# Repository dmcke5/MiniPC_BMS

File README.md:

# MiniPC BMS
A tiny UPS for powering Mini PC's from battery!

## Features:
- USB-C PD charging
- Secondary charger input
- USB-HID UPS communication to provide the operating system with battery information
- Inbuilt fuel gauge IC for accurate battery capacity monitoring
- Extremely low powered-down power consumption (5.1uA)
- Inbuilt 19v boost for stable output at up to 3A.
- Solid state switch for triggering PC power button

## Software:
The software for this project is based on this HID power device library:
https://github.com/abratchik/HIDPowerDevice

The software is complete and functional, although it could use some polish and some comments.
I would recommend changing the "debug" variable in MiniPC_UPS.ino to true before you flash the code for the first time.
This will enable debug output and stop the BMS from trying to shut your computer down due to a "Low battery".
Once you've confirmed all of the values are being read correctly, you should be safe to go back in and set that variable to false
and the BMS will begin functioning.

## Known issues

USB-C PD charging is slow. I found a small issue in the PCB design (which I have now fixed) before uploading that may or may not have solved this problem. I suspect that the issues I've had with this are just down to soldering or faulty hardware because the second charger input works as intended and it is basically identical to the first one after all of the USB PD components. I have checked and the correct values are being requested from the USB charger so the issue has somewhere down the line from the USB PD hardware. This was working for me at one stage, which is why I suspect its an assembly issue.

USB HID is sometimes not detected by windows. This one has been difficult to track down, but I'm certain its a software issue that's causing the problem. A simple restart of the system always seems to rectify the problem so I've left it alone for now.

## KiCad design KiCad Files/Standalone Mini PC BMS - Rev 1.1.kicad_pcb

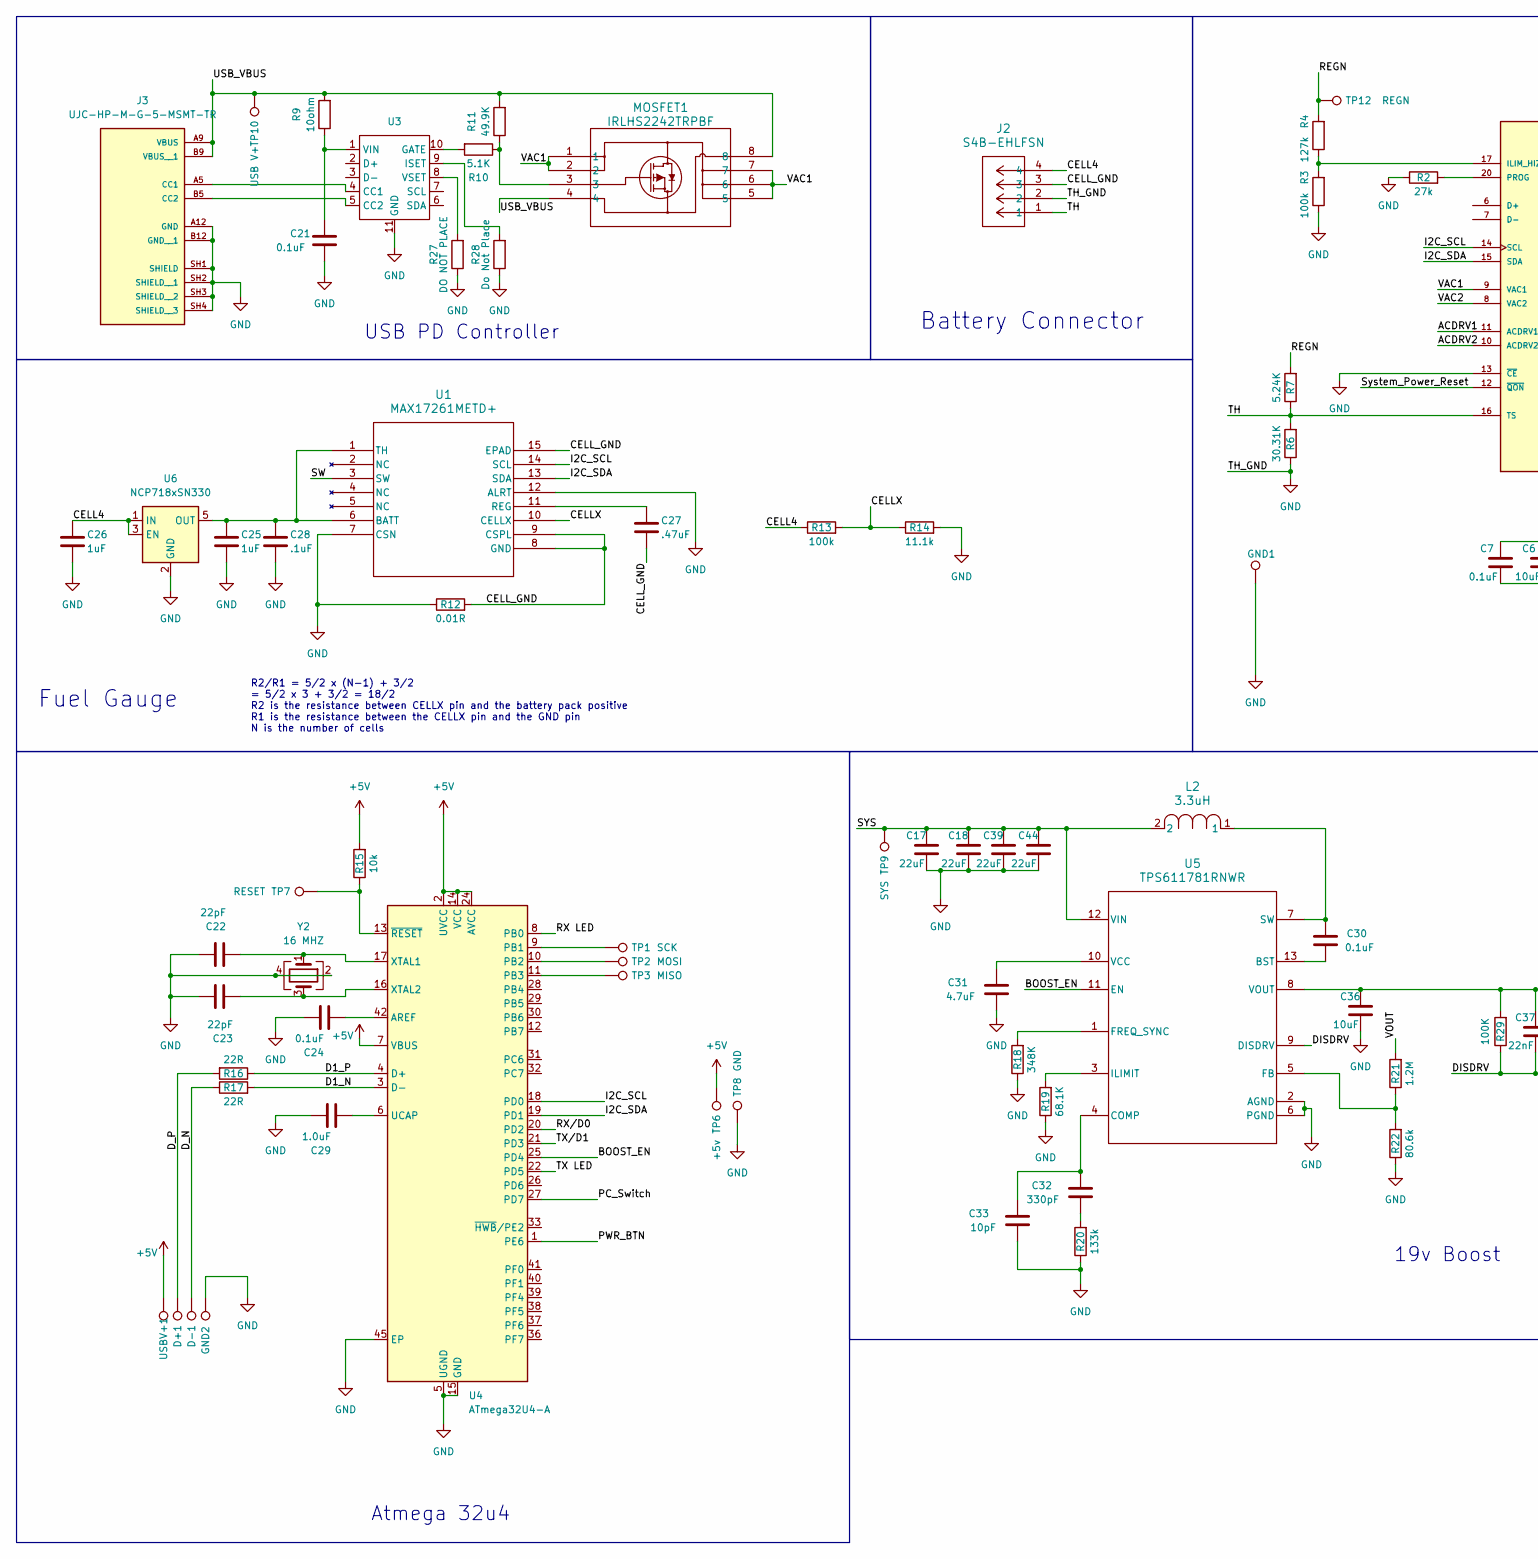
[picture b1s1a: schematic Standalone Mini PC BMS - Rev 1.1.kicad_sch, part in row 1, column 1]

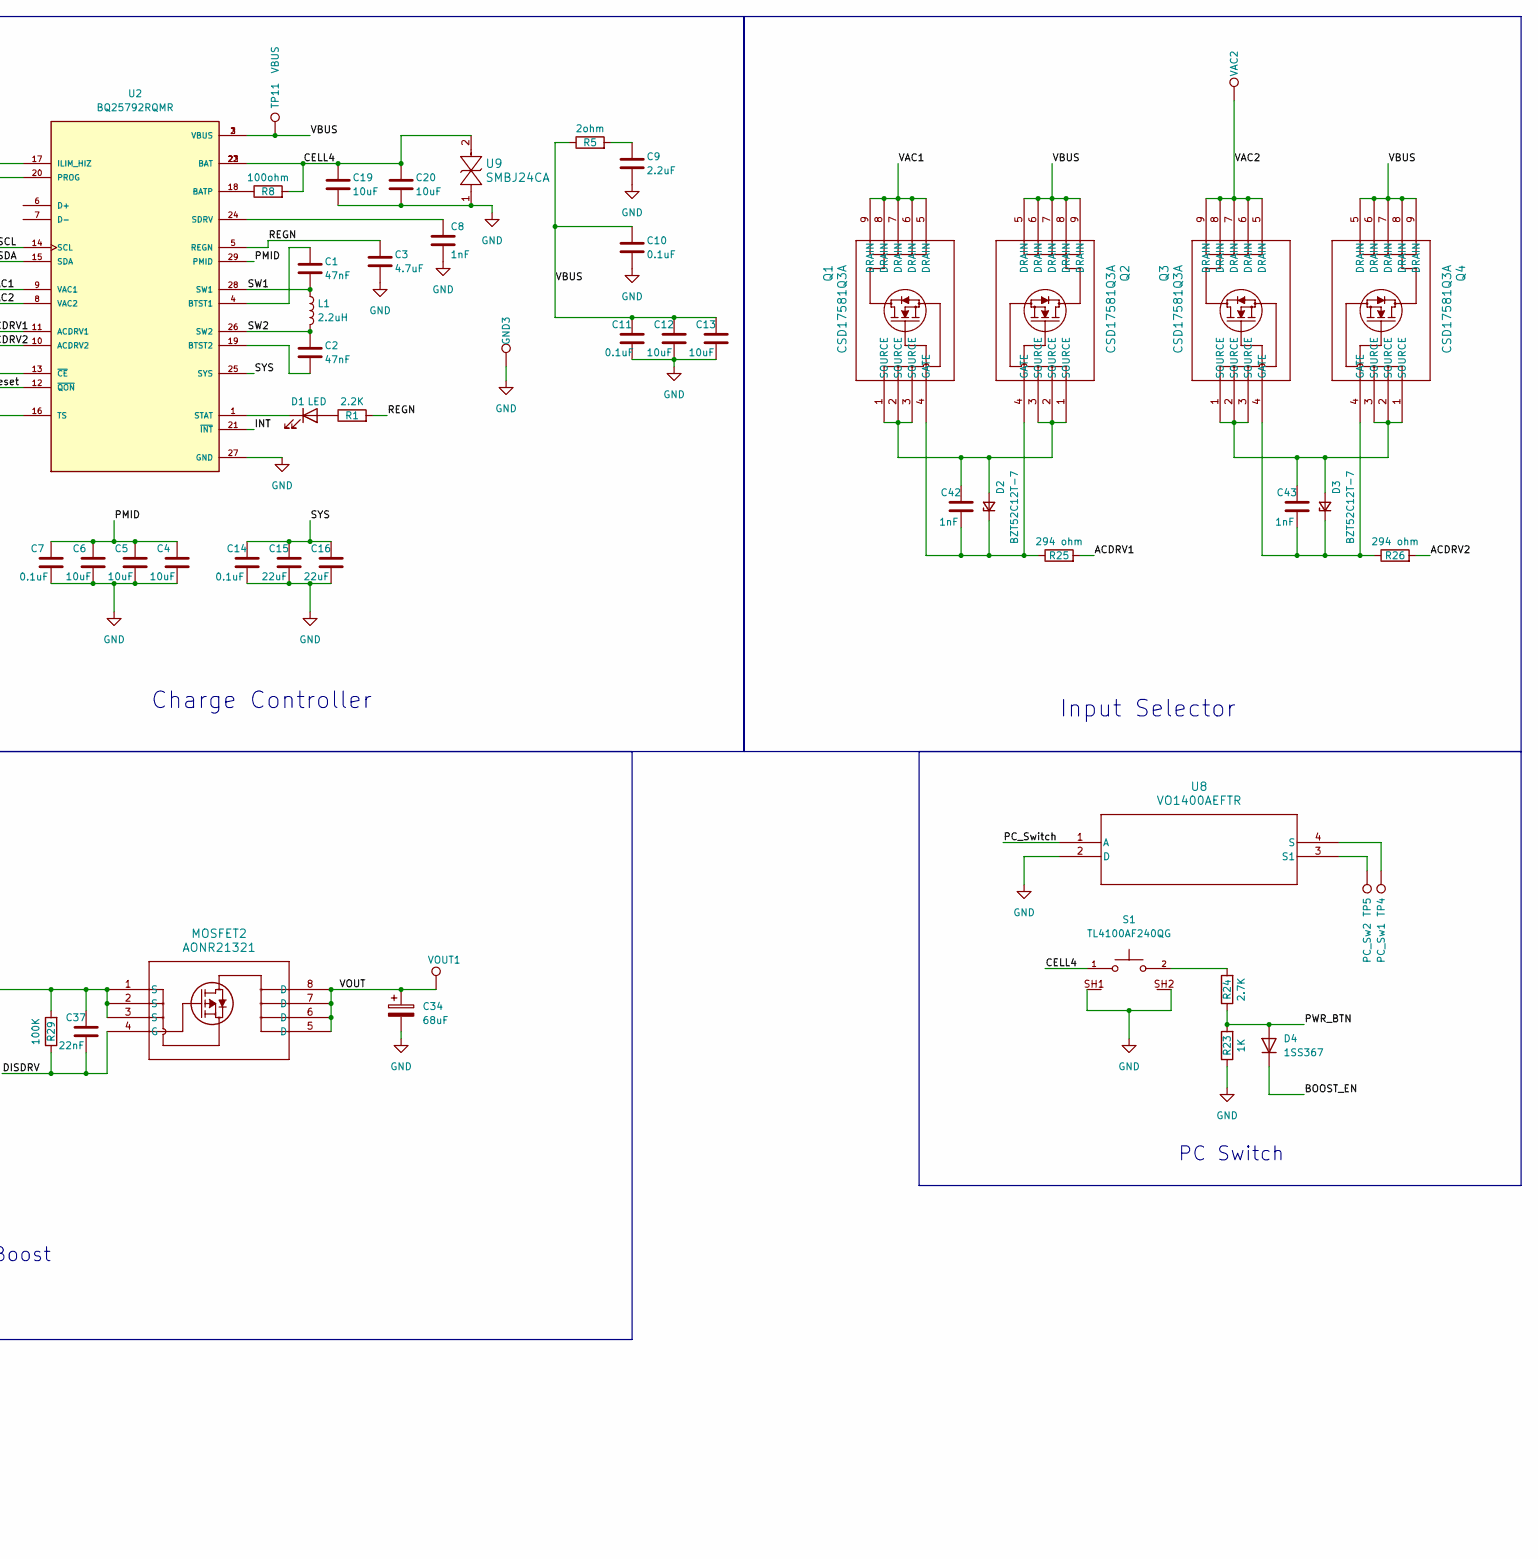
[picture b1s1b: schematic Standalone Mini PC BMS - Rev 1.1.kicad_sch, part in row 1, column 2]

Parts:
C1, C2: 47nF; C_0603_1608Metric
C3, C31: 4.7uF; C_0603_1608Metric
C4, C5, C6, C12, C13, C36: 10uF; C_0805_2012Metric
C7, C10, C11, C14, C24, C30: 0.1uF; C_0603_1608Metric
C8, C42, C43: 1nF; C_0603_1608Metric
C9: 2.2uF; C_0603_1608Metric
C15, C16, C17, C18, C39, C44: 22uF; C_0805_2012Metric
C19, C20: 10uF; C_0603_1608Metric
C21: 0.1uF; C_0603_1608Metric_Pad1.08x0.95mm_HandSolder
C22, C23: 22pF; C_0603_1608Metric
C25, C26: 1uF; C_0603_1608Metric
C27: .47uF; C_0603_1608Metric
C28: .1uF; C_0603_1608Metric
C29: 1.0uF; C_0603_1608Metric
C32: 330pF; C_0603_1608Metric
C33: 10pF; C_0603_1608Metric
C34: 68uF; CP_Radial_D5.0mm_P2.00mm
C37: 22nF; C_0603_1608Metric
D1: LED; LED_0603_1608Metric
D2, D3: BZT52C12T-7; SOD-523_0P9X1P3_ONS
D4: 1SS367; D_SOD-323
D+1: D+; TestPoint_THTPad_D1.5mm_Drill0.7mm
D-1: D-; TestPoint_THTPad_D1.5mm_Drill0.7mm
GND1: GND; TestPoint_THTPad_D2.0mm_Drill1.0mm
GND2, GND3: GND; TestPoint_THTPad_D1.5mm_Drill0.7mm
J2: S4B-EHLFSN; CONN_S4B-EHLFSN_JST
J3: UJC-HP-M-G-5-MSMT-TR; CUI_UJC-HP-M-G-5-MSMT-TR; PARTREV 1.01
L1: 2.2uH; IND_SPM6530_TDK
L2: 3.3uH; IND_1050-WE-HCI_WRE
MOSFET1: IRLHS2242TRPBF; PQFN6_2X2_INF
MOSFET2: AONR21321; DFN8_3x3_EP_AOS
Q1, Q2, Q3, Q4: CSD17581Q3A; Q3A_TEX
R1: 2.2K; R_0603_1608Metric
R2: 27k; R_0603_1608Metric
R3, R13: 100k; R_0603_1608Metric
R4: 127k; R_0603_1608Metric
R5: 2ohm; R_0603_1608Metric
R6: 30.31K; R_0603_1608Metric
R7: 5.24K; R_0603_1608Metric
R8: 100ohm; R_0603_1608Metric
R9: 10ohm; R_0603_1608Metric_Pad0.98x0.95mm_HandSolder
R10: 5.1K; R_0603_1608Metric_Pad0.98x0.95mm_HandSolder
R11: 49.9K; R_0603_1608Metric_Pad0.98x0.95mm_HandSolder
R12: 0.01R; R_2512_6332Metric
R14: 11.1k; R_0603_1608Metric
R15: 10k; R_0603_1608Metric
R16, R17: 22R; R_0603_1608Metric
R18: 348K; R_0603_1608Metric
R19: 68.1K; R_0603_1608Metric
R20: 133k; R_0603_1608Metric
R21: 1.2M; R_0603_1608Metric
R22: 80.6k; R_0603_1608Metric
R23: 1K; R_0603_1608Metric
R24: 2.7K; R_0603_1608Metric
R25, R26: 294 ohm; R_0603_1608Metric
R27: DO NOT PLACE; R_0603_1608Metric_Pad0.98x0.95mm_HandSolder
R28: Do Not Place; R_0603_1608Metric_Pad0.98x0.95mm_HandSolder
R29: 100K; R_0603_1608Metric
S1: TL4100AF240QG; SW_TL4100AF240QG; PARTREV C
TP1: SCK; TestPoint_Pad_D1.0mm
TP2: MOSI; TestPoint_Pad_D1.0mm
TP3: MISO; TestPoint_Pad_D1.0mm
TP4: PC_Sw1; TestPoint_THTPad_D1.5mm_Drill0.7mm
TP5: PC_Sw2; TestPoint_THTPad_D1.5mm_Drill0.7mm
TP6: +5v; TestPoint_Pad_D1.0mm
TP7: RESET; TestPoint_Pad_D1.0mm
TP8: GND; TestPoint_Pad_D1.0mm
TP9: SYS; TestPoint_Pad_D1.0mm
TP10: USB V+; TestPoint_Pad_D1.0mm
TP11: VBUS; TestPoint_Pad_D1.0mm
TP12: REGN; TestPoint_Pad_D1.0mm
U1: MAX17261METD+; 21-0137_T1433+2C_MXM
U2: BQ25792RQMR; QFN40P400X400X100-29N; PARTREV 11/2019
U3: DFN-10-1EP_3x3mm_P0.5mm_EP1.7x2.5mm
U4: ATmega32U4-A; QFN-44-1EP_7x7mm_P0.5mm_EP5.15x5.15mm
U5: TPS611781RNWR; RNW0013A
U6: NCP718xSN330; SOT-23-5
U8: VO1400AEFTR; SO-4_VO_VIS
U9: SMBJ24CA; SMBJ24CA_LTF
USBV+1: USB V+; TestPoint_THTPad_D1.5mm_Drill0.7mm
VAC2: VAC2; TestPoint_THTPad_D1.5mm_Drill0.7mm
VOUT1: V+ OUT; TestPoint_THTPad_D2.0mm_Drill1.0mm
Y2: 16 MHZ; Crystal_SMD_5032-4Pin_5.0x3.2mm

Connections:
+5V: R15.2, TP6.1, U4.2 (UVCC), U4.7 (VBUS), U4.14 (VCC), U4.24 (AVCC), U4.34 (VCC), U4.44 (AVCC), USBV+1.1
/ACDRV1: R25.2, U2.11 (ACDRV1)
/ACDRV2: R26.2, U2.10 (ACDRV2)
/BOOST_EN: D4.1 (K), U4.25 (PD4), U5.11 (EN)
/CELL4: C19.1, C20.1, C26.1, J2.4, R8.2, R13.1, S1.1, U2.22 (BAT), U2.23 (BAT), U6.1 (IN), U6.3 (EN), U9.2
/CELLX: R13.2, R14.1, U1.10 (CELLX)
/CELL_GND: C27.2, J2.3, R12.2, U1.8 (GND), U1.9 (CSPL), U1.15 (EPAD)
/D1_N: R17.2, U4.3 (D-)
/D1_P: R16.1, U4.4 (D+)
/DISDRV: C37.2, MOSFET2.4 (G), R29.1, U5.9 (DISDRV)
/D_N: D-1.1, R17.1
/D_P: D+1.1, R16.2
/I2C_SCL: U1.14 (SCL), U2.14 (SCL), U4.18 (PD0)
/I2C_SDA: U1.13 (SDA), U2.15 (SDA), U4.19 (PD1)
/INT: U2.21 (~INT)
/PC_Switch: U4.27 (PD7), U8.1 (A)
/PMID: C4.1, C5.1, C6.1, C7.1, U2.29 (PMID)
/PWR_BTN: D4.2 (A), R23.2, R24.1, U4.1 (PE6)
/REGN: C3.1, R1.2, R4.2, R7.2, TP12.1, U2.5 (REGN)
/RX LED: U4.8 (PB0)
/RX/D0: U4.20 (PD2)
/SW: U1.3 (SW)
/SW1: C1.2, L1.1, U2.28 (SW1)
/SW2: C2.1, L1.2, U2.26 (SW2)
/SYS: C14.1, C15.1, C16.1, C17.1, C18.1, C39.1, C44.1, L2.2, TP9.1, U2.25 (SYS), U5.12 (VIN)
/System_Power_Reset: U2.12 (~QON)
/TH: J2.1, R6.2, R7.1, U2.16 (TS)
/TX LED: U4.22 (PD5)
/TX/D1: U4.21 (PD3)
/USB_VBUS: J3.A9 (VBUS), J3.B9 (VBUS__1), MOSFET1.4, MOSFET1.8, R9.2, R11.2, TP10.1
/VAC1: MOSFET1.1, MOSFET1.2, MOSFET1.5, MOSFET1.6, MOSFET1.7, Q1.5 (DRAIN), Q1.6 (DRAIN), Q1.7 (DRAIN), Q1.8 (DRAIN), Q1.9 (DRAIN), U2.9 (VAC1)
/VAC2: Q3.5 (DRAIN), Q3.6 (DRAIN), Q3.7 (DRAIN), Q3.8 (DRAIN), Q3.9 (DRAIN), U2.8 (VAC2), VAC2.1
/VBUS: C10.1, C11.1, C12.1, C13.1, Q2.5 (DRAIN), Q2.6 (DRAIN), Q2.7 (DRAIN), Q2.8 (DRAIN), Q2.9 (DRAIN), Q4.5 (DRAIN), Q4.6 (DRAIN), Q4.7 (DRAIN), Q4.8 (DRAIN), Q4.9 (DRAIN), R5.1, TP11.1, U2.2 (VBUS), U2.3 (VBUS)
/VOUT: C34.1, MOSFET2.5 (D), MOSFET2.6 (D), MOSFET2.7 (D), MOSFET2.8 (D), R21.2, VOUT1.1
GND: C3.2, C4.2, C5.2, C6.2, C7.2, C8.2, C9.2, C10.2, C11.2, C12.2, C13.2, C14.2, C15.2, C16.2, C17.2, C18.2, C19.2, C20.2, C21.2, C22.1, C23.1, C24.1, C25.2, C26.2, C28.2, C29.1, C31.1, C33.1, C34.2, C36.2, C39.2, C44.2, GND1.1, GND2.1, GND3.1, J2.2, J3.A12 (GND), J3.B12 (GND__1), J3.SH1 (SHIELD), J3.SH2 (SHIELD__1), J3.SH3 (SHIELD__2), J3.SH4 (SHIELD__3), R2.1, R3.1, R6.1, R12.1, R14.2, R18.1, R19.1, R20.1, R22.1, R23.1, R27.1, R28.1, S1.SH1, S1.SH2, TP8.1, U1.7 (CSN), U1.12 (ALRT), U2.13 (~CE), U2.27 (GND), U3.11 (GND), U4.5 (UGND), U4.15 (GND), U4.23 (GND), U4.35 (GND), U4.43 (GND), U4.45 (EP), U5.2 (AGND), U5.6 (PGND), U6.2 (GND), U8.2 (D), U9.1, Y2.2, Y2.4
unnamed: C9.1, R5.2
unnamed: C32.1, R20.2
unnamed: D1.2 (A), R1.1
unnamed: D1.1 (K), U2.1 (STAT)
unnamed: C42.1, D2.2 (A), Q1.1 (SOURCE), Q1.2 (SOURCE), Q1.3 (SOURCE), Q2.1 (SOURCE), Q2.2 (SOURCE), Q2.3 (SOURCE)
unnamed: C42.2, D2.1 (K), Q1.4 (GATE), Q2.4 (GATE), R25.1
unnamed: C43.1, D3.2 (A), Q3.1 (SOURCE), Q3.2 (SOURCE), Q3.3 (SOURCE), Q4.1 (SOURCE), Q4.2 (SOURCE), Q4.3 (SOURCE)
unnamed: C43.2, D3.1 (K), Q3.4 (GATE), Q4.4 (GATE), R26.1
unnamed: J3.A5 (CC1), U3.4 (CC1)
unnamed: J3.B5 (CC2), U3.5 (CC2)
unnamed: MOSFET1.3, R10.1, R11.1
unnamed: R24.2, S1.2
unnamed: C25.1, C28.1, U1.1 (TH), U1.6 (BATT), U6.5 (OUT)
unnamed: C27.1, U1.11 (REG)
unnamed: R8.1, U2.18 (BATP)
unnamed: C1.1, U2.4 (BTST1)
unnamed: C2.2, U2.19 (BTST2)
unnamed: R3.2, R4.1, U2.17 (ILIM_HIZ)
unnamed: R2.2, U2.20 (PROG)
unnamed: C8.1, U2.24 (SDRV)
unnamed: R10.2, U3.10 (GATE)
unnamed: R28.2, U3.9 (ISET)
unnamed: C21.1, R9.1, U3.1 (VIN)
unnamed: R27.2, U3.8 (VSET)
unnamed: C24.2, U4.42 (AREF)
unnamed: TP1.1, U4.9 (PB1)
unnamed: TP2.1, U4.10 (PB2)
unnamed: TP3.1, U4.11 (PB3)
unnamed: C29.2, U4.6 (UCAP)
unnamed: C22.2, U4.17 (XTAL1), Y2.1
unnamed: C23.2, U4.16 (XTAL2), Y2.3
unnamed: R15.1, TP7.1, U4.13 (~RESET)
unnamed: C30.1, U5.13 (BST)
unnamed: C32.2, C33.2, U5.4 (COMP)
unnamed: R21.1, R22.2, U5.5 (FB)
unnamed: R18.2, U5.1 (FREQ_SYNC)
unnamed: R19.2, U5.3 (ILIMIT)
unnamed: C30.2, L2.1, U5.7 (SW)
unnamed: C31.2, U5.10 (VCC)
unnamed: C36.1, C37.1, MOSFET2.1 (S), MOSFET2.2 (S), MOSFET2.3 (S), R29.2, U5.8 (VOUT)
unnamed: TP5.1, U8.3 (S1)
unnamed: TP4.1, U8.4 (S)

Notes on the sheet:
USB PD Controller
19v Boost
Atmega 32u4
PC Switch
Input Selector
Fuel Gauge
R2/R1 = 5/2 x (N-1) + 3/2 = 5/2 x 3 + 3/2 = 18/2 R2 is the resistance between CELLX pin and the battery pack positive R1 is the resistance between the CELLX pin and the GND pin N is the number of cells
Battery Connector
Charge Controller

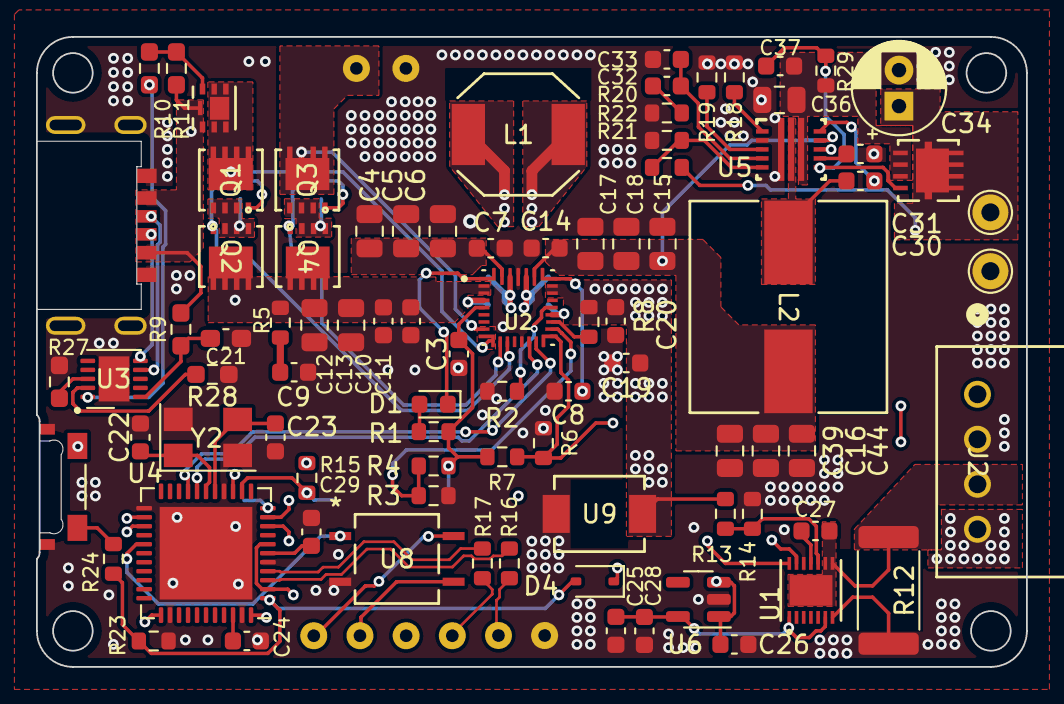
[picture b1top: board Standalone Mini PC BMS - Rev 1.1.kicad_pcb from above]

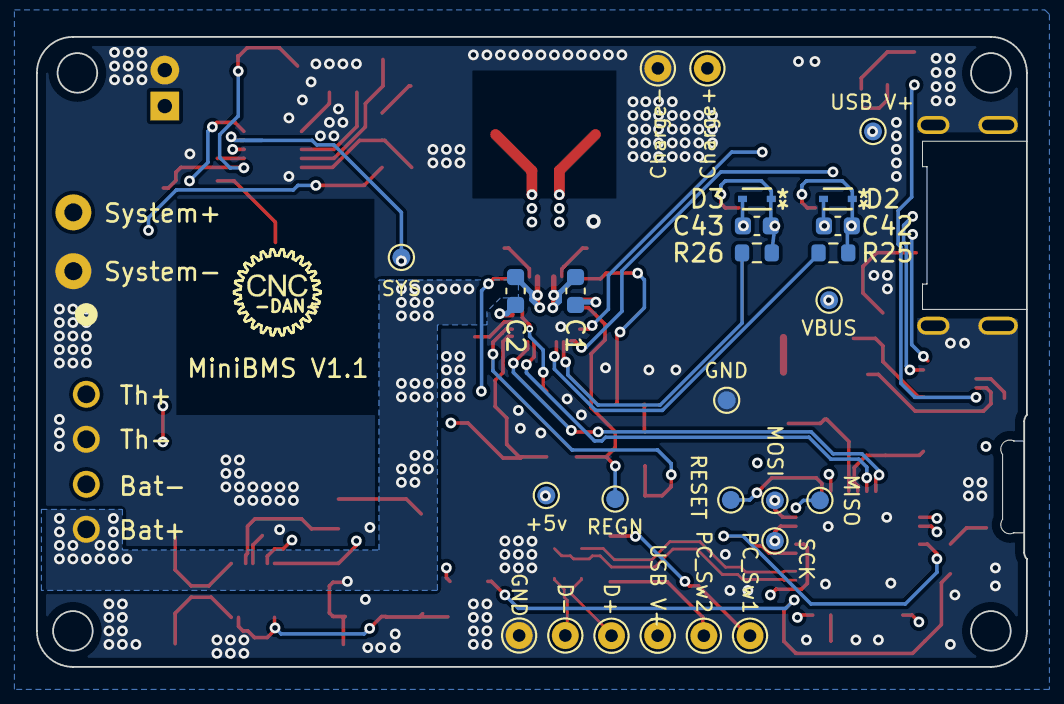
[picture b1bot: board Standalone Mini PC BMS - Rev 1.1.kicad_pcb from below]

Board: 4 copper layers, 55.0 x 35.0 mm, 113 parts (26 on the bottom side), 70 nets.

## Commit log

2025-06-22 Create Licence
2025-07-02 Added Project Files
2025-07-17 Fixed filled zone on net D2-A
2025-07-17 Added image
2025-07-17 Updated image
2025-07-17 Added software and known issues to readme
